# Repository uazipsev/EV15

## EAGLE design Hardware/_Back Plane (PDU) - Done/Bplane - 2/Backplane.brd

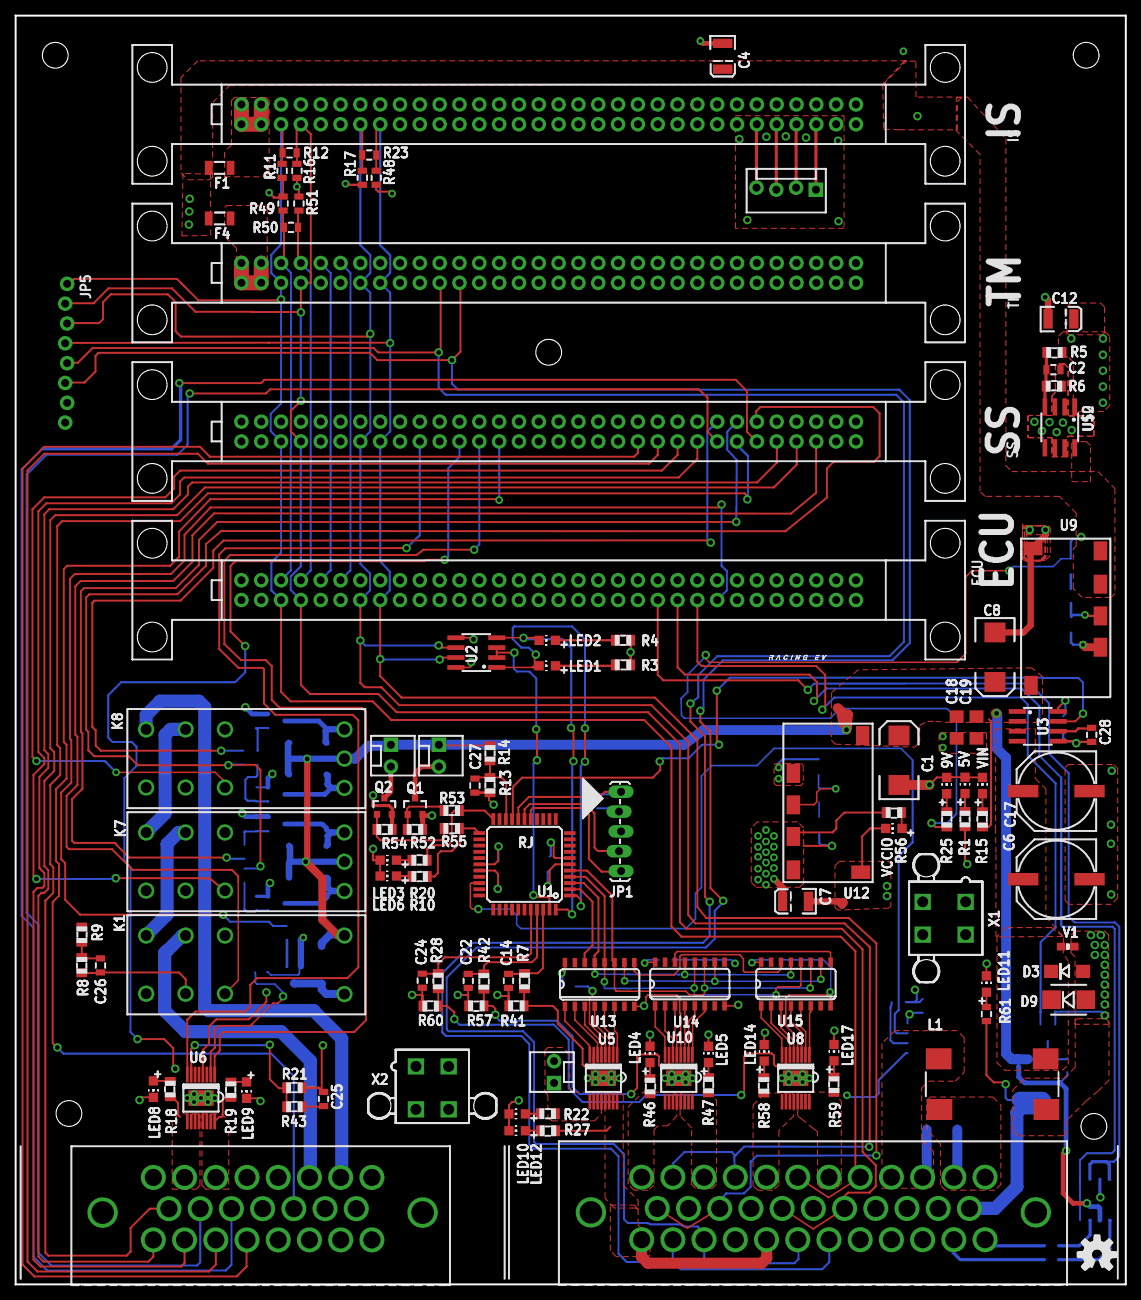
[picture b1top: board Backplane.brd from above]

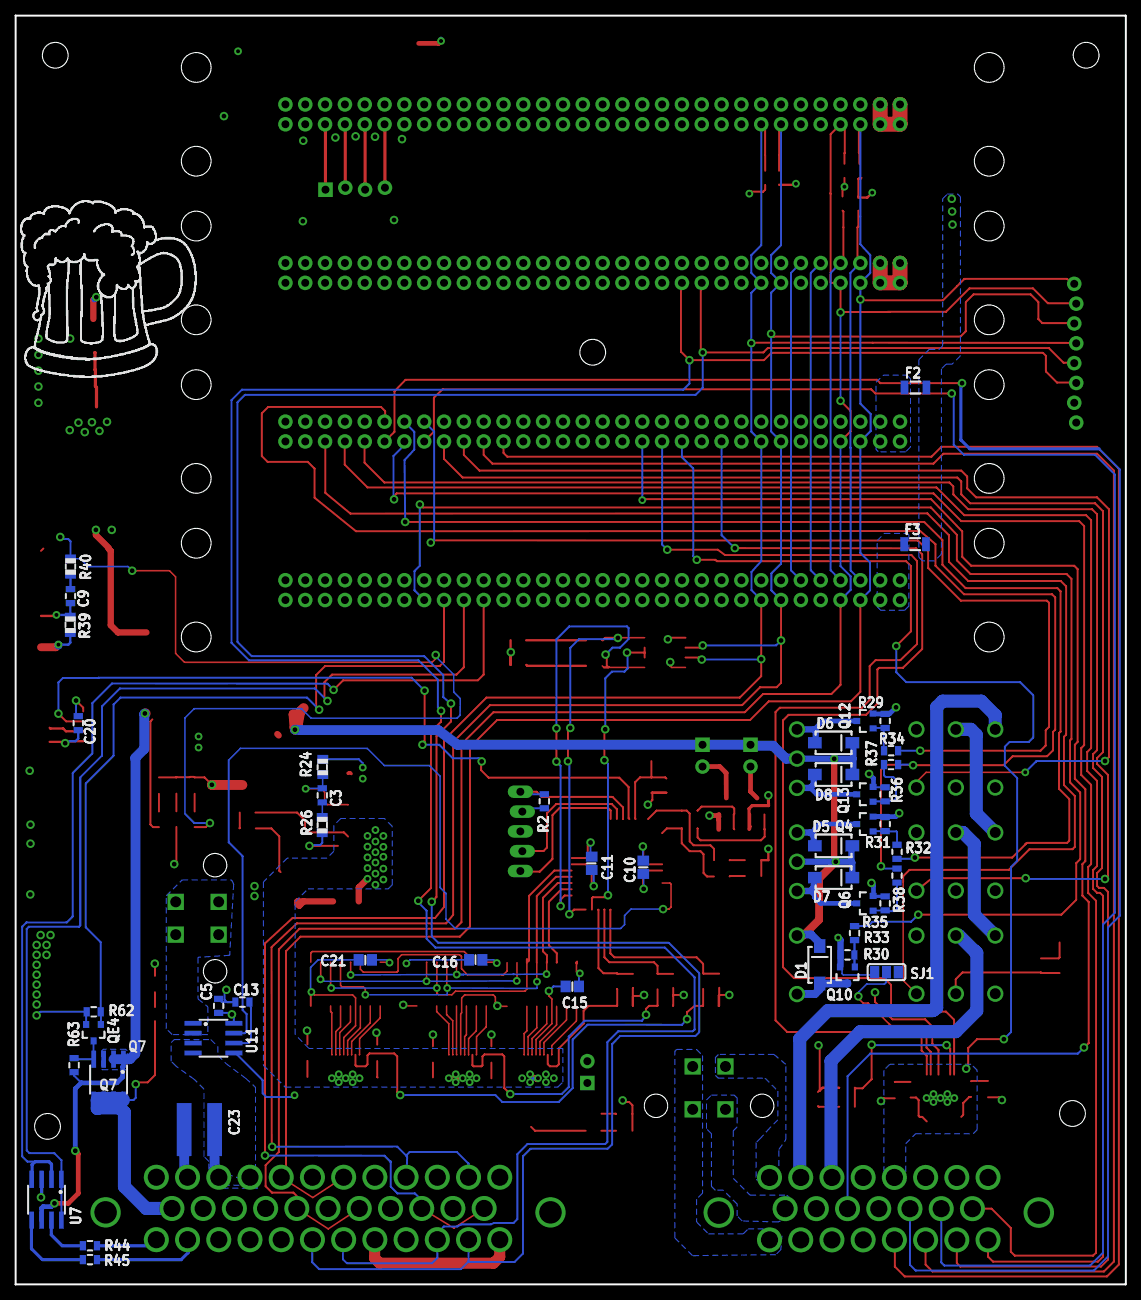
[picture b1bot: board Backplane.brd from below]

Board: 4 copper layers, 142.2 x 162.6 mm, 172 parts (48 on the bottom side), 153 nets.

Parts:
5V, 9V: Green; CHIP-LED0805
C1, C8: 10uF; EIA7343
C2, C5, C13, C20: 0.1uF; 0805
C3: DNP; 0805
C4, C7, C12: 10uF; EIA3528
C6, C17: 100uF; PANASONIC_G
C9: dnp; 0805
C10, C11, C15, C16, C21: .1uF; C0805
C14, C22, C24, C25: 10nF; 0805
C18, C19: 1uf; 1206
C23: 1000pf; C1825
C26, C27: 1uF; 0805
C28: .1uF; 0805
D1, D5, D6, D7, D8: ES1AE-TP; SMA-DIODE-KIT
D3: TVS; DO-214AC
D9: 30V; SMB-DIODE
F1, F2, F3, F4: PTCSMD; PTC-1206
J1: M23; 1-770669-1
J2: M35; 1-776163-2
JP1: 1X05_LOCK_LONGPADS
JP2, JP3, JP4: M02POLAR_LOCK; MOLEX-1X2_LOCK
JP5: 1X08_LOCK_NO_SILK
JP7: Headphone; MOLEX-1X4_LOCK
K1: RTE44024F
K7, K8: RT424F24
L1: ACM1513-551-2PL-TL
LED1, LED4, LED5, LED6, LED8, LED9, LED10, LED12, LED14, LED17: green; CHIP-LED0805
LED2, LED3: red; CHIP-LED0805
LED11: CHIP-LED0805
Q1, Q2, Q4, Q6, Q10, Q12, Q13: BSS123; SOT23-3
Q7: Si9435BDY; SO08
QE4: BSS123; SOT-23
R1, R3, R4, R5, R6, R7, R10, R18, R19, R20, R21, R22, R27, R28, R41, R42, R43, R46, R47, R53, R55, R57, R58, R59, R60: 1k; R0805
R2, R29, R30, R31, R35, R36, R62: 10k; 0805
R8, R13: 24k; R0805
R9, R14: 91k; R0805
R11, R16, R17, R48, R49, R51: 523; 0805
R12, R23, R50: 120; 0805
R15, R25, R56: 1.21k; R0805
R24, R39: 8.43k; R0805
R26, R40: dnp; R0805
R32, R33, R34, R37, R38: 1k; 0805
R44, R45: 0; 0805
R52, R54: 100k; R0805
R61: 2.2k; 0805
R63: 22k; 0805
SJ1: PAD-JUMPER-3-NO_YES_SILK_FULL_BOX
STANDOFF1, STANDOFF2, STANDOFF3, STANDOFF4, STANDOFF5: STAND-OFF
U1: PIC18F45K22; TQFP-44
U2: SN75HVD08DR; SO-8
U3, U11: ACS712; SO-8
U5, U6, U8, U10: VND7040AJTR-E; SSO-16-POWER
U7: FAN3278TMX; SO-8
U9, U12: APXW005A0X43-SRZ
U13, U14, U15: 74LS595D; SO16
U$1, U$4, U$5, U$6: CARD-SLOT; CS64
U$2: LM2931; SO08
U$3: BEERL; B-L
U$7: LOGO; L-MS
U$8: OSHW-LOGOM; OSHW-LOGO-M
U$9: INDPK1; PICKIT-PIN-1
V1: 30V; 0603-RES
VCCIO: Green; CHIP-LED0805
VIN: Green; CHIP-LED0805
X1, X2: 5566-4

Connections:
1AVAL: C22.1, R42.1, U1.41
2AVAL: C24.1, R28.1, U1.40
3AVAL: C14.1, R7.1, U1.42
+5V: C5.1, C10.1, C11.1, C12.A, C15.1, C16.1, C20.1, C21.1, JP1.2, R1.2, R2.2, R3.2, R4.2, R5.2, R11.2, R17.2, R49.2, U1.7, U1.28, U2.8, U3.8, U11.8, U13.16, U14.16, U15.16, U$2.1
+9V: C4.A, F1.2, F2.2, F3.2, F4.2, R25.2, R40.1, U9.5, U9.6, U$2.8
+24V: C1.A, C8.A, C18.1, C19.1, D1.C, D5.C, D6.C, D7.C, D8.C, JP3.1, JP4.1, K1.A1, K7.A3, K8.A3, Q7.1, Q7.2, Q7.3, R14.2, R15.2, R63.2, U3.1, U3.2, U7.6, U9.2, U12.2
AIR-BOT+PRE: J1.3, R19.2, U6.13, U6.14, U6.15, U6.16
AIR-P: J1.8, X2.1
AIR-TOP: J1.2, R18.2, U6.9, U6.10, U6.11, U6.12
AMD-SEN: J1.17, U$6.28
B-LIGHT: J2.23, Q7.5, Q7.6, Q7.7, Q7.8, R61.2
B-LIGHT-C: QE4.1, R62.2, U$1.24
BMS-P: J2.1, R46.2, U10.9, U10.10, U10.11, U10.12
BOTS-SEN: J1.16, U$6.29
BPD-R-SET: R34.2, U$6.57
BPD-SEN: K8.22, U$6.23
CLEAR: U13.10, U14.10, U15.10
CLK: U1.5, U13.11, U14.11, U15.11
CSENSE: U1.19, U3.7
DATA-IN: U1.2, U13.14
DDS-P: J2.7, R59.2, U8.13, U8.14, U8.15, U8.16
ECU-RELAY: R33.2, U$1.25
ECU-SEN: K1.22, U$6.30
FAN: J1.15, X2.3
FROM-TSMS: J1.4, U6.EP, U$6.12
GND: 5V.C, 9V.C, C1.C, C2.2, C4.C, C5.2, C6.-, C7.C, C8.C, C10.2, C11.2, C12.C, C13.2, C14.2, C15.2, C16.2, C17.-, C18.2, C19.2, C20.2, C21.2, C22.2, C24.2, C25.2, C26.2, C27.2, C28.2, D3.A, D9.A, J2.14, J2.16, J2.18, J2.20, J2.22, J2.27, J2.31, JP1.3, JP5.7, JP5.8, K1.21, K7.21, K8.21, L1.OUT-, LED3.C, LED4.C, LED5.C, LED6.C, LED8.C, LED9.C, LED10.C, LED11.C, LED12.C, LED14.C, LED17.C, Q1.2, Q2.2, Q4.2, Q6.2, Q10.2, Q12.2, Q13.2, QE4.2, R6.1, R8.1, R13.1, R16.1, R21.2, R24.2, R29.1, R30.1, R31.1, R35.1, R36.1, R39.2, R41.2, R48.1, R51.1, R52.1, R54.1, R57.2, R60.2, R62.1, SJ1.3, U1.6, U1.29, U2.5, U3.5, U5.4, U6.4, U7.3, U8.4, U9.1, U9.3, U10.4, U11.5, U12.1, U12.3, U13.8, U14.8, U15.8, U$1.31, U$1.32, U$1.63, U$1.64, U$2.2, U$2.3, U$2.6, U$2.7, U$4.31, U$4.32, U$4.63, U$4.64, U$5.31, U$5.32, U$5.63, U$5.64, U$6.31, U$6.32, U$6.63, U$6.64, V1.1, VCCIO.C, VIN.C
H-EN: U7.1, U7.8, U$1.23
H-SIG: U7.2, U7.4, U$1.22
HCMESURE: U1.31, U11.7
HORN+: J2.35, R44.2
HORN-: J2.34, R45.2
IMD-INPUT: J1.13, U$6.14
IMD-R-SET: R32.2, U$6.58
IMD-SEN: K7.22, U$6.24
IS-SEN: J1.18, U$6.22
LAT: U1.4, U13.12, U14.12, U15.12
LED1: R20.2, R53.2, U1.22
LED2: R10.2, R55.2, U1.23
LOOP-IN: J1.6, K1.11
MAIN: U6.8, U$6.10
MCS-P: J2.3, R47.2, U10.13, U10.14, U10.15, U10.16
unnamed: R56.1, VCCIO.A
unnamed: LED8.A, R18.1
unnamed: C2.1, R5.1, R6.2, U$2.4
unnamed: U10.8, U14.1
unnamed: F1.1, U$5.1, U$5.2, U$5.33, U$5.34
unnamed: Q4.1, R31.2, R32.1
unnamed: K1.14, K7.11
unnamed: 9V.A, R25.1
unnamed: F2.1, U$6.1, U$6.2, U$6.33, U$6.34
unnamed: LED9.A, R19.1
unnamed: R21.1, R43.2, U6.7
unnamed: F3.1, U$1.1, U$1.2, U$1.33, U$1.34
unnamed: F4.1, U$4.1, U$4.2, U$4.33, U$4.34
unnamed: SJ1.2, U6.2
unnamed: K7.14, K8.11
unnamed: LED3.A, R20.1
unnamed: JP2.1, JP2.2, R22.2, U5.9, U5.10, U5.11, U5.12
unnamed: C28.1, U3.6
unnamed: 5V.A, R1.1
unnamed: JP7.1, U$5.30
unnamed: JP3.2, Q1.3
unnamed: JP4.2, Q2.3
unnamed: Q6.1, R35.2, R38.2
unnamed: LED1.A, R3.1
unnamed: LED2.A, R4.1
unnamed: Q1.1, R52.2, R53.1
unnamed: Q2.1, R54.2, R55.1
unnamed: LED10.A, R22.1
unnamed: LED12.A, R27.1
unnamed: C6.+, C17.+, D3.C, D9.C, L1.OUT+, U3.3, U3.4, V1.2
unnamed: R7.2, R41.1, U5.7
unnamed: Q7.4, QE4.3, R63.1
unnamed: U10.6, U14.2
unnamed: LED11.A, R61.1
unnamed: C3.1, R26.2
unnamed: U10.5, U14.3
unnamed: C3.2, R24.1, U12.4
unnamed: JP7.2, U$5.29
unnamed: U10.3, U14.4
unnamed: JP1.4, U1.17
unnamed: U$1.38, U$4.38
unnamed: R15.1, VIN.A
unnamed: JP1.5, U1.16
unnamed: U10.2, U14.5
unnamed: D1.A, K1.A2, Q10.3
unnamed: JP1.1, R2.1, U1.18
unnamed: D5.A, K7.A1, Q4.3
unnamed: Q10.1, R30.2, R33.1
unnamed: D7.A, K7.A2, Q6.3
unnamed: D6.A, K8.A1, Q12.3
unnamed: D8.A, K8.A2, Q13.3
unnamed: R44.1, U7.7
unnamed: R45.1, U7.5
unnamed: LED6.A, R10.1
unnamed: Q13.1, R36.2, R37.2
unnamed: JP7.3, U$5.28
unnamed: U$1.37, U$4.37
unnamed: Q12.1, R29.2, R34.1
unnamed: C9.1, R40.2
unnamed: C9.2, R39.1, U9.4
unnamed: U11.1, U11.2, X1.1, X1.2, X1.3, X1.4
unnamed: U10.1, U14.6
unnamed: C13.1, U11.6
unnamed: U8.8, U15.1
unnamed: U8.6, U15.2
unnamed: U8.5, U15.3
unnamed: LED4.A, R46.1
unnamed: LED5.A, R47.1
unnamed: R42.2, R57.1, U10.7
unnamed: U8.3, U15.4
unnamed: U8.2, U15.5
unnamed: U8.1, U15.6
unnamed: U5.8, U13.1
unnamed: U5.6, U13.2
unnamed: U5.5, U13.3
unnamed: U5.3, U13.4
unnamed: U5.2, U13.5
unnamed: U5.1, U13.6
unnamed: U13.9, U15.14
unnamed: U14.14, U15.9
unnamed: JP7.4, U$5.27
unnamed: LED14.A, R58.1
unnamed: LED17.A, R59.1
unnamed: R28.2, R60.1, U8.7
OUTEN: U1.3, U13.13, U14.13, U15.13
P+F: J1.23, X2.2
PRE+: U6.1, U$6.13
RAVAL: C25.1, R43.1
RELAY-SET: R37.1, R38.1, U$6.59
RS1-A: J2.6, J2.8, JP5.1, R11.1, R12.2, U$1.3, U$4.3, U$5.3, U$6.3
RS1-B: J2.17, J2.19, JP5.2, R12.1, R16.2, U$1.4, U$4.4, U$5.4, U$6.4
RS2-A: J2.2, J2.4, JP5.3, R17.1, R23.2, U2.6, U$1.7, U$4.7, U$5.7, U$6.7
RS2-B: J2.13, J2.15, JP5.4, R23.1, R48.2, U2.7, U$1.8, U$4.8, U$5.8, U$6.8
RS3-A: R49.1, R50.2, U$1.35, U$4.35
RS3-B: R50.1, R51.2, U$1.36, U$4.36
RX: LED1.C, U1.1, U2.1
SAS-P: J2.5, R58.2, U8.9, U8.10, U8.11, U8.12
SSW_C_SEN: J1.10, U$6.25
SSW_L-SEN: J1.11, U$6.27
SSW_R-SEN: J1.9, U$6.26
TO-TSMS: J1.7, K8.14
TSA: J2.25, J2.30, JP5.5, U$4.11
TSB: J2.26, J2.29, JP5.6, U$4.12
TSMS-SEN: J1.19, U$6.21
TSS-P: J2.24, J2.28, R27.2, U5.13, U5.14, U5.15, U5.16
TX: LED2.C, U1.44, U2.4
U2-CNT: U1.43, U2.2, U2.3
VCCIO: C7.A, R26.1, R56.2, U5.EP, U8.EP, U10.EP, U12.5, U12.6
VGND: C23.2, J2.11, J2.12, L1.IN-
VIN: C23.1, J2.9, J2.10, L1.IN+, U11.3, U11.4
VSENSE: C27.1, R13.2, R14.1, U1.20
VSENSE2: C26.1, R8.2, R9.1

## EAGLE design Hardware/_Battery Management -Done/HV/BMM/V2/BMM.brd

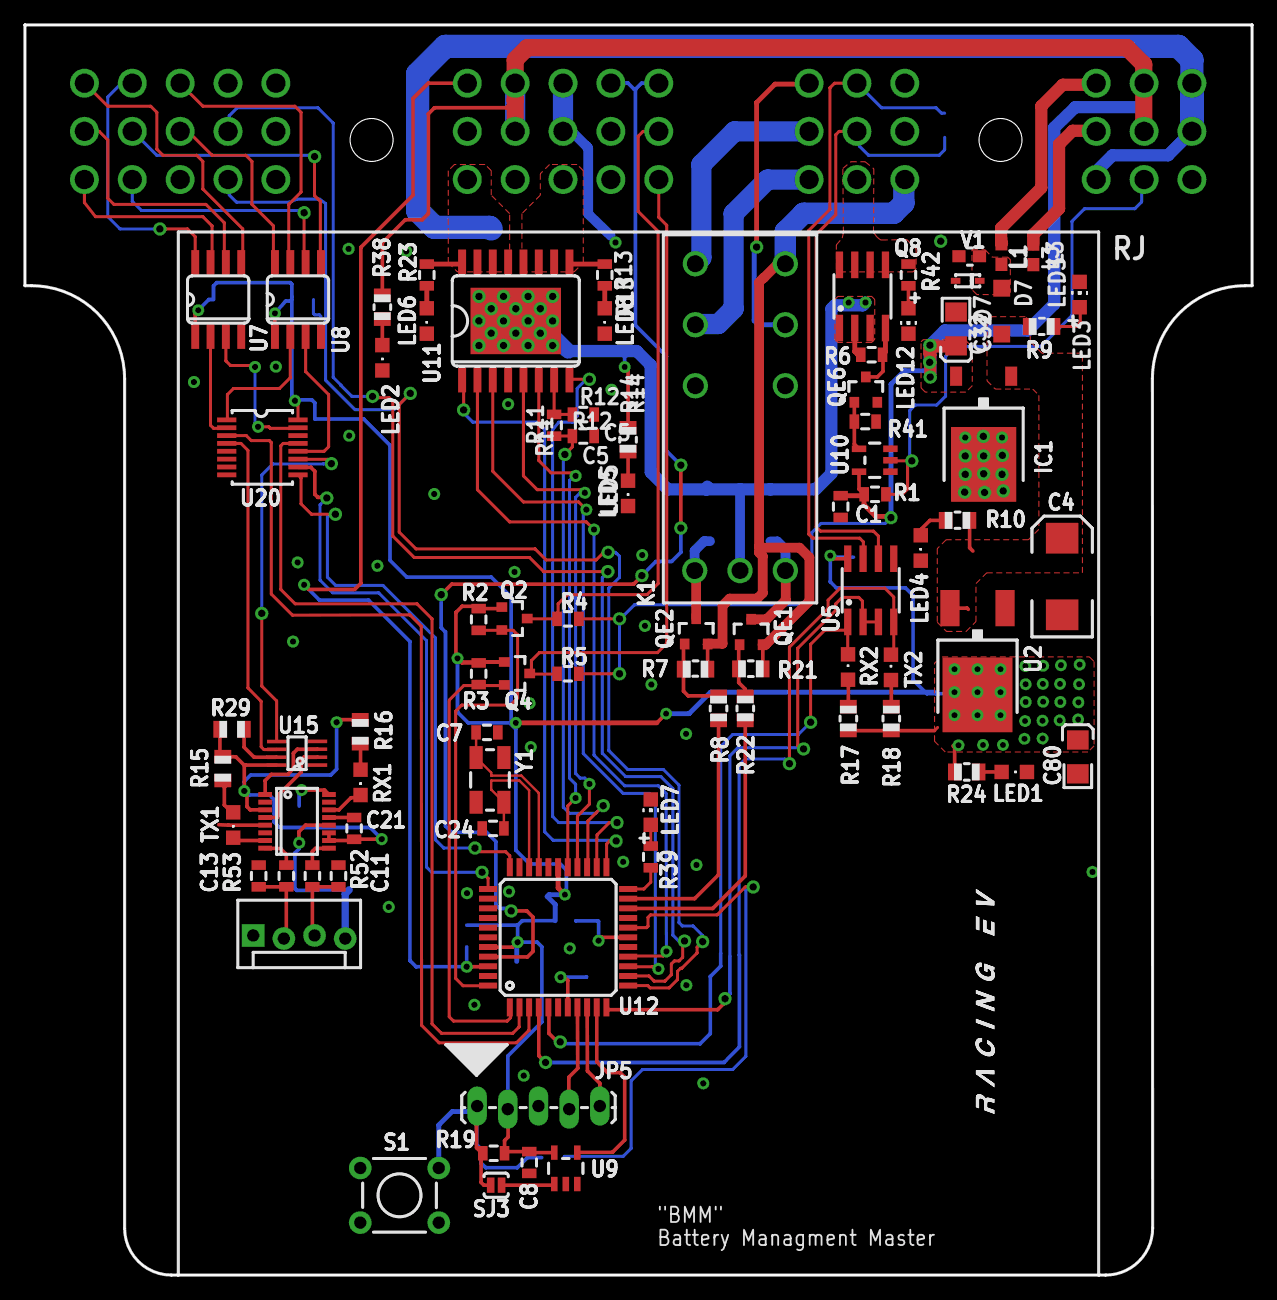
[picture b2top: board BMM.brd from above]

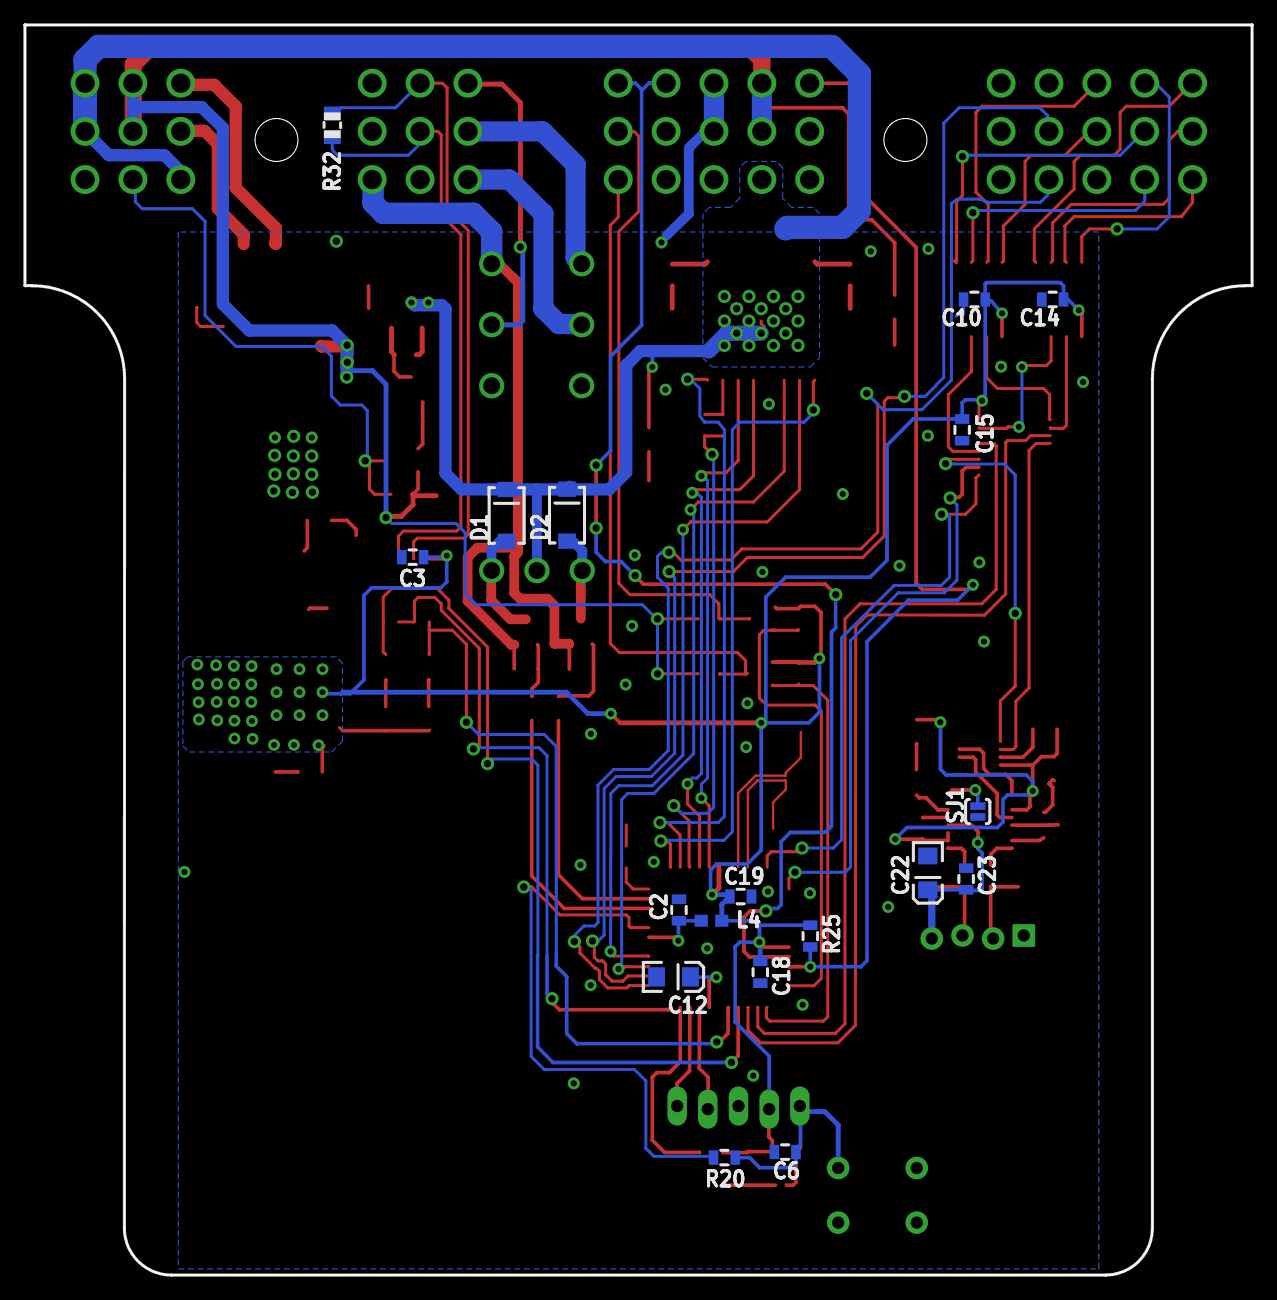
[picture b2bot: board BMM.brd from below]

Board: 2 copper layers, 101.6 x 103.5 mm, 104 parts (18 on the bottom side), 99 nets.

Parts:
C1, C3, C8, C10, C14, C15, C21, C23: 0.1uf; 0805
C2, C18, C19: 0.1uF; 0805
C4: 100uF; EIA7343
C5: 0805
C6: 10nF; 0805
C7, C24: 12pF; 0805
C11, C13: 47pf; 0805
C12: 10uF; EIA3216
C22: 4.7uF; EIA3216
C32, C80: 10uF; POLC1206
CASE1: 581-01-48-009
D1, D2: SMA-DIODE
D3: MM5Z30; SOD-523F
D7: 1N4001; SOD123
IC1: 7805DT; TO252
JP5: ICSP; 1X05_LOCK_LONGPADS
JP13: MOLEX-1X4_LOCK
K1: RT424F24
L1, L3, L4: FB; 0603
LED1, LED2, LED4, LED5: Green; CHIPLED_0805
LED3, LED7, LED12: CHIP-LED0805
LED6, LED8: CHIPLED_0805
Q2, Q4: BSS123; SOT23-3
Q8: Si9435BDY; SO08
QE1, QE2, QE6: BSS123; SOT-23
R1: 1k; 0805
R2, R3: 2k; 0805
R4, R5, R11, R19, R25: 10k; 0805
R6: 22k; 0805
R7, R21: 100K; R0805
R8, R15, R17, R22, R29: 1K; R0805
R9, R10: 1.2k; R0805
R12: 0805
R13, R23: 3.3k; 0805
R14: 3.3k; R0805
R16, R18, R38: 1k; R0805
R20, R39: 499; 0805
R24: 499; R0805
R32: 120; R0805
R41: 100k; 0805
R42: 2.2k; 0805
R52, R53: 27; 0805
RX1: CHIPLED_0805
RX2: RED; CHIPLED_0805
S1: ts; TACTILE-PTH
SJ1: PAD-JUMPER-2-NO_YES_SILK
SJ3: SJ-NO; SJ_2S-NO
TX1: CHIPLED_0805
TX2: GREEN; CHIPLED_0805
U2: NCP1117DT33T5G; V-REG_DPACK
U4: SN74LVC2G241DCTR; VFSOP-8
U5: SN75HVD08DR; SO-8
U7, U8: ISL83077; SO08
U9: MAX823; SOT23-5L
U10: NC7S14M5X; SOT23-5
U11: VND7040AJTR-E; SO-16-POWER
U12: DSPIC33FJ128GP804; TQFP-44
U15: FT230X; SSOP-16
U20: CD74HC4052PWR; TSSOP-16
U$1: LOGOM; L-M
U$2: INDPK1; PICKIT-PIN-1
V1: 13Vdc; 0603
Y1: 12Mhz; CRYSTAL-SMD-5X3

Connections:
3V: C21.1, R15.2, R16.2, R29.2, U4.8, U15.3, U15.10, U15.11
!FLT: U11.2, U12.15
+3V3: C3.1, C8.1, C10.1, C14.1, C15.1, C18.1, C19.1, C80.1, JP5.2, L4.2, Q2.1, Q4.1, R2.2, R3.2, R17.2, R18.2, R19.2, R24.2, R25.2, U2.4, U5.8, U7.1, U8.1, U9.5, U12.28, U12.40, U20.16
+5V: C1.1, C32.1, CASE1.19, CASE1.20, CASE1.43, CASE1.44, IC1.2, R1.2, R4.2, R5.2, R38.2, U10.5
+9V: C4.A, D7.C, IC1.1, R9.2, R10.2, U2.3
ASEN: C5.1, R11.2, U12.25
BMS-P-EN: CASE1.25, CASE1.28, U12.41
BMS-RX: U12.3, U20.3
BMS-RXB1: U8.2, U20.1
BMS-RXB2: U7.2, U20.2
BMS-SET: R8.1, U12.21
BMS-SS: R22.2, U12.20
BMS-TX: U12.2, U20.13
BMS-TXB1: U8.3, U20.12
BMS-TXB2: U7.3, U20.15
BOX1-TALK: CASE1.12, U12.12
BOX2-TALK: CASE1.11, U12.13
C_N: C7.1, U12.30, Y1.1
C_P: C24.1, U12.31, Y1.3
FAN1: CASE1.24, R13.2, U11.9, U11.10, U11.11, U11.12
FAN1-EN: U11.1, U12.23
FAN2: CASE1.18, R23.2, U11.13, U11.14, U11.15, U11.16
FAN2-EN: U11.8, U12.24
FAN-SS: CASE1.16, R25.1, U12.42
GND: C1.2, C2.2, C3.2, C4.C, C5.2, C6.2, C7.2, C8.2, C10.2, C11.2, C12.C, C13.2, C14.2, C15.2, C18.2, C19.2, C21.2, C22.C, C23.2, C24.2, C32.2, C80.2, CASE1.22, CASE1.23, D3.A, IC1.3, JP5.3, JP13.1, L3.2, LED1.C, LED2.C, LED3.C, LED4.C, LED5.C, LED6.C, LED7.C, LED8.C, LED12.C, QE6.2, R12.1, R41.1, S1.1, SJ1.1, U2.1, U4.1, U4.4, U5.5, U7.4, U8.4, U9.2, U10.3, U11.4, U12.6, U12.16, U12.29, U12.39, U15.5, U15.13, U20.6, U20.7, U20.8, V1.1
GNDIO: CASE1.41, L3.1
HV-SENSE: CASE1.45, R1.1, U10.2
unnamed: LED8.A, R13.1
unnamed: D1.A, K1.A1, QE1.3
unnamed: LED1.A, R24.1
unnamed: D2.A, K1.A2, QE2.3
unnamed: LED6.A, R23.1
unnamed: QE2.1, R7.2, R8.2
unnamed: LED3.A, R9.1
unnamed: R11.1, R12.2, U11.7
unnamed: LED4.A, R10.1
unnamed: LED5.A, R14.1
unnamed: CASE1.33, K1.21
unnamed: R52.2, U15.9
unnamed: R15.1, TX1.A
unnamed: R16.1, RX1.A
unnamed: TX1.C, U15.7
unnamed: RX1.C, U15.14
unnamed: R18.1, TX2.A
unnamed: U4.2, U15.4
unnamed: U4.3, U15.1
unnamed: LED2.A, R38.1
unnamed: LED7.A, R39.1
unnamed: CASE1.1, U7.5
unnamed: SJ3.1, U9.1
unnamed: C2.1, L4.1, U12.17
unnamed: C12.A, U12.7
unnamed: QE1.1, R21.2, R22.1
unnamed: CASE1.2, U7.6
unnamed: CASE1.3, U7.7
unnamed: CASE1.4, U7.8
unnamed: CASE1.5, U8.5
unnamed: CASE1.32, K1.24
unnamed: CASE1.6, U8.6
unnamed: CASE1.7, U8.7
unnamed: CASE1.8, U8.8
unnamed: R17.1, RX2.A
unnamed: CASE1.31, K1.11
unnamed: Q8.4, QE6.3, R6.1
unnamed: R39.2, U12.22
unnamed: C6.1, JP5.1, R19.1, R20.1, S1.3, SJ3.2
unnamed: R20.2, U12.18
unnamed: JP5.4, U12.8
unnamed: JP5.5, U12.9
unnamed: LED12.A, R42.1
unnamed: R53.2, U15.8
unnamed: C11.1, JP13.3, R52.1
unnamed: C13.1, JP13.2, R53.1
unnamed: SJ1.2, U15.16
unnamed: D3.C, D7.A, L1.2, V1.2
unnamed: R29.1, U4.7
unnamed: U4.6, U20.4
unnamed: U4.5, U20.11
unnamed: C22.A, C23.1, JP13.4, U15.12
RS-A: CASE1.35, R32.1, U5.6
RS-B: CASE1.34, R32.2, U5.7
RX2: RX2.C, U5.1, U12.5
S0: U12.34, U20.10
S1: U12.33, U20.9
SCL: Q2.2, R2.1, U12.44
SCL_5V: CASE1.29, Q2.3, R4.1
SDA: Q4.2, R3.1, U12.1
SDA_5V: CASE1.30, Q4.3, R5.1
SEN0: U11.5, U12.26
SEN1: U11.6, U12.27
SEN_EN: U11.3, U12.14
TSAL: CASE1.36, Q8.5, Q8.6, Q8.7, Q8.8, R42.2
TSAL_EN: QE6.1, R41.2, U10.4
TX2: TX2.C, U5.4, U12.4
U5-RE/DE: U5.2, U5.3, U12.11
V+: CASE1.21, CASE1.42, CASE1.46, CASE1.47, D1.C, D2.C, K1.A3, Q8.1, Q8.2, Q8.3, R6.2, R14.2, U11.EP
VCCIO: CASE1.40, L1.1
VSS: CASE1.39, K1.14, QE1.2, QE2.2, R7.1, R21.1
WDI: U9.4, U12.10

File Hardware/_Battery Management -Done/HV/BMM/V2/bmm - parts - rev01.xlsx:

Part | qty | Value | Device | Package
R52 | 2 | 27 | RESISTOR0805-RES | 805
R32 | 1 | 120 | R-US_R0805 | R0805
R20 | 3 | 499 | RESISTOR0805-RES | 805
C1 | 11 | 0.1uf | CAP0805 | 805
R9 | 2 | 1.2k | R-US_R0805 | R0805
R7 | 3 | 100K | R-US_R0805 | R0805
C4 | 1 | 100uF | CAP_POL7343 | EIA7343
R4 | 5 | 10k | RESISTOR0805-RES | 805
C6 | 1 | 10nF | CAP0805 | 805
C12 | 1 | 10uF | 10UF-TANT | EIA3216
C32 | 2 | 10uF | POLCAP | POLC1206
Y1 | 1 | 12Mhz | CRYSTAL5X3 | CRYSTAL-SMD-5X3
C7 | 2 | 12pF | CAP0805 | 805
V1 | 1 | 13Vdc | VAR-RES | 603
R1 | 9 | 1k | RESISTOR0805-RES | 805
D7 | 1 | 1N4001 | DIODE-SOD123 | SOD123
R42 | 1 | 2.2k | RESISTOR0805-RES | 805
R6 | 1 | 22k | RESISTOR0805-RES | 805
R2 | 2 | 2k | RESISTOR0805-RES | 805
R13 | 3 | 3.3k | RESISTOR0805-RES | 805
C22 | 1 | 4.7uF | CAP_POL1206 | EIA3216
C11 | 2 | 47pf | CAP0805 | 805
IC1 | 1 | 7805DT | 7805DT | TO252
Q2 | 5 | BSS123 | MOSFET-NCHANNELBSS123LT1G | SOT23-3
U20 | 1 | CD74HC4052PWR | CD74HC4052PWR | TSSOP-16
D1 | 2 | DIODESMA | SMA-DIODE | SparkFun-DiscreteSemi
U12 | 1 | DSPIC33FJ128GP804 | DSPIC33FJ128GP804 | TQFP-44
L1 | 3 | FB | FERITEBEAD | 603
U15 | 1 | FT230X | FT230X | SSOP-16
U7 | 2 | ISL83077 | ISL83077 | SO08
U9 | 1 | MAX823 | MAX823 | SOT23-5L
D3 | 1 | MM5Z30 | MM5Z30 | SOD-523F
U10 | 1 | NC7S14M5X | NC7S14M5X | SOT23-5
U2 | 1 | NCP1117DT33T5G | V_REG_317DPACK | V-REG_DPACK
K1 | 1 | RT424F24 | RT424F24 | RT424F24
Q8 | 1 | Si9435BDY | MOSFET-PCHANNEL-SOIC8SOIC8 | SO08
U4 | 1 | SN74LVC2G241DCTR | SN74LVC2G241DCTR | VFSOP-8
U5 | 1 | SN75HVD08DR | SN75HVD08DR | SO-8
S1 | 1 | ts | SWITCH-MOMENTARY-2PTH | TACTILE-PTH
U11 | 1 | VND7040AJTR-E | VND7040AJTR-E | SO-16-POWER
LED1 |  | Green | LEDCHIPLED_0805 | CHIPLED_0805
LED2 |  | Green | LEDCHIPLED_0805 | CHIPLED_0805
LED4 |  | Green | LEDCHIPLED_0805 | CHIPLED_0805
LED5 |  | Green | LEDCHIPLED_0805 | CHIPLED_0805
TX2 |  | GREEN | LEDCHIPLED_0805 | CHIPLED_0805
LED6 |  | LEDCHIPLED_0805 | CHIPLED_0805 | adafruit
LED8 |  | LEDCHIPLED_0805 | CHIPLED_0805 | adafruit
RX1 |  | LEDCHIPLED_0805 | CHIPLED_0805 | adafruit
TX1 |  | LEDCHIPLED_0805 | CHIPLED_0805 | adafruit
LED3 |  | LEDCHIP-LED0805 | CHIP-LED0805 | adafruit
LED7 |  | LEDCHIP-LED0805 | CHIP-LED0805 | adafruit
LED12 |  | LEDCHIP-LED0805 | CHIP-LED0805 | adafruit
RX2 |  | RED | LEDCHIPLED_0805 | CHIPLED_0805
R12 |  | RESISTOR0805-RES | 805 | SparkFun-Passives
C5 | 1 | CAP0805 | 805 | SparkFun-Passives

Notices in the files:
parts and their libraries:
SparkFun: Licensing: CC v3.0 Share-Alike You are welcome to use this library for commercial purposes.
SparkFun-Passives: Licensing: Creative Commons ShareAlike 4.0 International - https://creativecommons.org/licenses/by-sa/4.0
